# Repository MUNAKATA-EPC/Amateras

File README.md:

Munako_Amateras
2026年度：サッカーライトウェイトリーグ出場
2027年度：サッカーオープンリーグ出場予定

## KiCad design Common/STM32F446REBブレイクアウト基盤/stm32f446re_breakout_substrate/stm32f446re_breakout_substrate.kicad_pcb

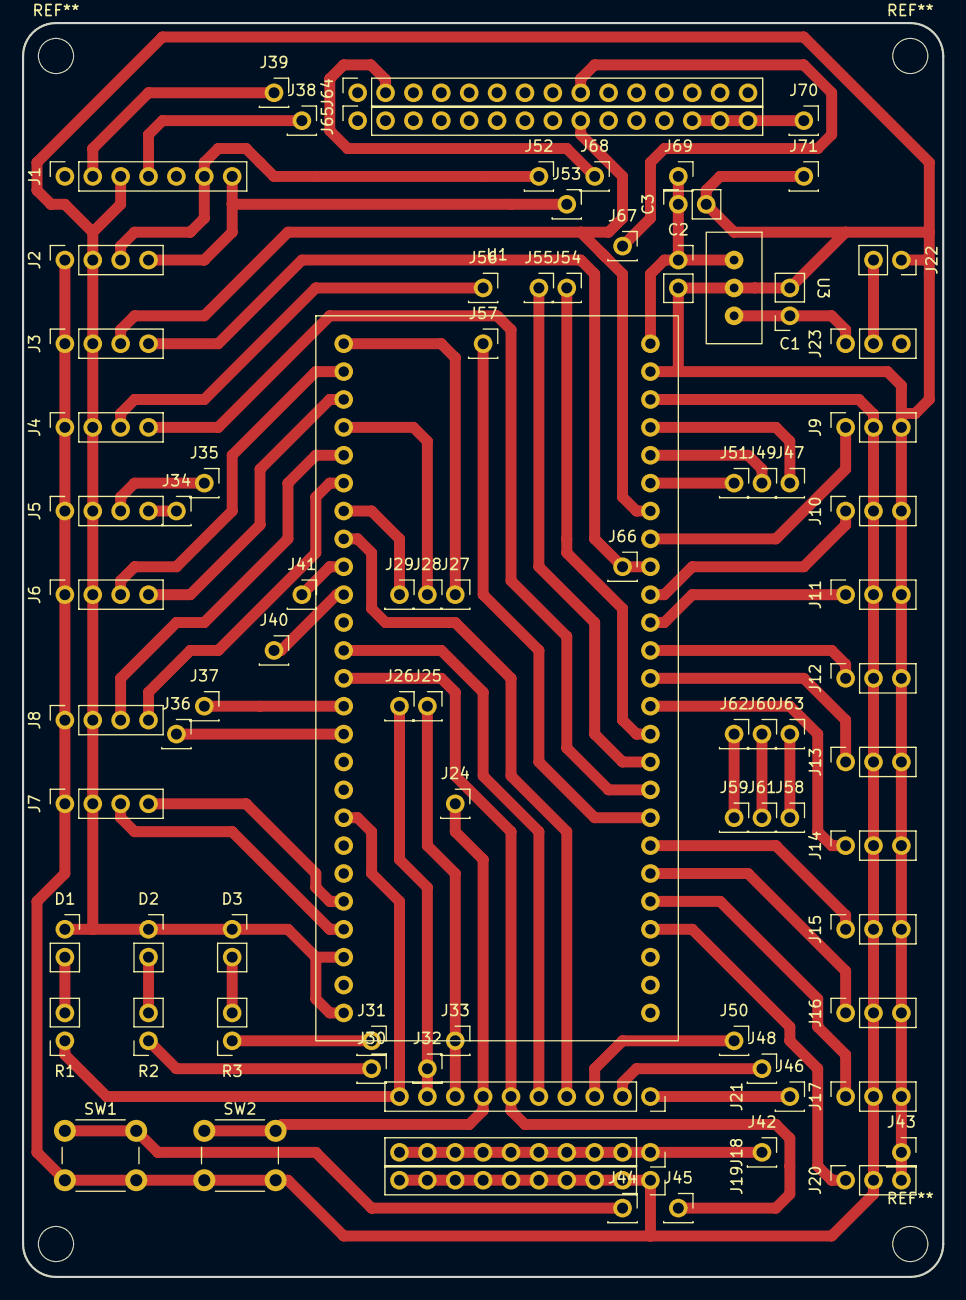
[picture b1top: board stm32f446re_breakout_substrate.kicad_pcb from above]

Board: 2 copper layers, 83.8 x 114.2 mm, 84 parts (0 on the bottom side), 67 nets.

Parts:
C1, C2: C; PinSocket_1x02_P2.54mm_Vertical
C3: C_Polarized; PinSocket_1x02_P2.54mm_Vertical
D1, D2, D3: LED; PinSocket_1x02_P2.54mm_Vertical
J1: Conn_01x07_Socket; PinSocket_1x07_P2.54mm_Vertical
J2, J3, J4, J5, J6, J7, J8: Conn_01x04_Socket; PinSocket_1x04_P2.54mm_Vertical
J9, J10, J11, J12, J13, J14, J15, J16, J17, J20, J23: Conn_01x03_Socket; PinSocket_1x03_P2.54mm_Vertical
J18, J19, J21: Conn_01x10_Socket; PinSocket_1x10_P2.54mm_Vertical
J22: Conn_01x02_Socket; PinSocket_1x02_P2.54mm_Vertical
J24: J1_B; PinSocket_1x01_P2.54mm_Vertical
J25: J2_B; PinSocket_1x01_P2.54mm_Vertical
J26: J3_B; PinSocket_1x01_P2.54mm_Vertical
J27: J1_A; PinSocket_1x01_P2.54mm_Vertical
J28: J2_A; PinSocket_1x01_P2.54mm_Vertical
J29: J3_A; PinSocket_1x01_P2.54mm_Vertical
J30: J4_B; PinSocket_1x01_P2.54mm_Vertical
J31: J5_B; PinSocket_1x01_P2.54mm_Vertical
J32: J4_A; PinSocket_1x01_P2.54mm_Vertical
J33: J5_A; PinSocket_1x01_P2.54mm_Vertical
J34: J6_B; PinSocket_1x01_P2.54mm_Vertical
J35: J7_B; PinSocket_1x01_P2.54mm_Vertical
J36: J6_A; PinSocket_1x01_P2.54mm_Vertical
J37: J7_A; PinSocket_1x01_P2.54mm_Vertical
J38: J9_B; PinSocket_1x01_P2.54mm_Vertical
J39: J8_B; PinSocket_1x01_P2.54mm_Vertical
J40: J8_A; PinSocket_1x01_P2.54mm_Vertical
J41: J9_A; PinSocket_1x01_P2.54mm_Vertical
J42: J10_B; PinSocket_1x01_P2.54mm_Vertical
J43: J10_A; PinSocket_1x01_P2.54mm_Vertical
J44: J11_B; PinSocket_1x01_P2.54mm_Vertical
J45: J11_A; PinSocket_1x01_P2.54mm_Vertical
J46: J12_B; PinSocket_1x01_P2.54mm_Vertical
J47: J12_A; PinSocket_1x01_P2.54mm_Vertical
J48: J13_B; PinSocket_1x01_P2.54mm_Vertical
J49: J13_A; PinSocket_1x01_P2.54mm_Vertical
J50: J14_B; PinSocket_1x01_P2.54mm_Vertical
J51: J14_A; PinSocket_1x01_P2.54mm_Vertical
J52: J16_B; PinSocket_1x01_P2.54mm_Vertical
J53: J15_B; PinSocket_1x01_P2.54mm_Vertical
J54: J15_A; PinSocket_1x01_P2.54mm_Vertical
J55: J16_A; PinSocket_1x01_P2.54mm_Vertical
J56: J17_B; PinSocket_1x01_P2.54mm_Vertical
J57: J17_A; PinSocket_1x01_P2.54mm_Vertical
J58, J63: J18_A; PinSocket_1x01_P2.54mm_Vertical
J59, J62: J19_A; PinSocket_1x01_P2.54mm_Vertical
J60, J61: J20_A; PinSocket_1x01_P2.54mm_Vertical
J64, J65: Conn_01x15_Socket; PinSocket_1x15_P2.54mm_Vertical
J66: J21_A; PinSocket_1x01_P2.54mm_Vertical
J67: J21_B; PinSocket_1x01_P2.54mm_Vertical
J68: J22_B; PinSocket_1x01_P2.54mm_Vertical
J69: J22_A; PinSocket_1x01_P2.54mm_Vertical
J70: J23_B; PinSocket_1x01_P2.54mm_Vertical
J71: J23_A; PinSocket_1x01_P2.54mm_Vertical
R1, R2, R3: R; PinSocket_1x02_P2.54mm_Vertical
SW1, SW2: SW_Push; SW_PUSH_6mm_H5mm
U1: STM32F446RE
U3: TO220F

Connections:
+3V3: J2.1, J3.1, J4.1, J5.1, J6.1, J7.1, J8.1, J9.2, J10.2, J11.2, J12.2, J13.2, J14.2, J15.2, J16.2, J17.2, J19.1, J19.2, J19.3, J19.4, J19.5, J19.6, J19.7, J19.8, J19.9, J19.10, J20.2, SW1.2, SW2.2, U1.3 (3V3)
+5V: C2.1, C3.1, J69.1, U1.1 (5V), U3.2 (OUT)
+9V: J22.2, J23.2
Analog/PA4: J14.1, U1.14 (Analog/PA4)
Analog/PA5: J13.1, U1.13 (Analog/PA5)
Analog/PA6: J12.1, U1.12 (Analog/PA6)
Analog/PA7: J11.1, U1.11 (Analog/PA7)
Analog/PB1: J9.1, U1.8 (Analog/PB1)
Analog/PC0: J20.1, U1.22 (Analog/PC0)
Analog/PC1: J17.1, U1.21 (Analog/PC1)
Analog/PC2: J16.1, U1.20 (Analog/PC2)
Analog/PC3: J15.1, U1.19 (Analog/PC3)
Analog/PC4: J10.1, U1.10 (Analog/PC4)
Digital/PA11: J29.1, U1.32 (Digital/PA11)
Digital/PA11/sub: J21.9, J26.1, J32.1
Digital/PA12: J21.4, U1.33 (Digital/PA12)
Digital/PB5: J21.10, R1.1, U1.43 (Digital/PB5)
Digital/PB12: J51.1, U1.6 (Digital/PB12)
Digital/PB13: J49.1, U1.5 (Dgital/PB13)
Digital/PB14: J47.1, U1.4 (Digital/PB14)
Digital/PB15: J27.1, U1.26 (Digital/PB15)
Digital/PB15/sub: J21.7, J24.1, SW2.1
Digital/PC8: J28.1, U1.29 (Digital/PC8)
Digital/PC8/sub: J21.8, J25.1, J33.1
Digital/PC10: J21.5, U1.37 (Digital/PC10)
Digital/PC11: J21.6, J45.1, U1.38 (Digital/PC11)
GND: C1.2, C2.2, C3.2, D1.1 (K), D2.1 (K), D3.1 (K), J1.3, J2.2, J3.2, J4.2, J5.2, J6.2, J7.2, J8.2, J9.3, J10.3, J11.3, J12.3, J13.3, J14.3, J15.3, J16.3, J17.3, J20.3, J22.1, J43.1, J71.1, U1.2 (GND), U1.48 (GND), U1.50 (GND), U3.3 (GND)
Main9V: C1.1, J23.1, U3.1 (IN)
unnamed: D1.2 (A), R1.2
unnamed: D2.2 (A), R2.2
unnamed: D3.2 (A), R3.2
unnamed: J1.2, J39.1
unnamed: J1.4, J38.1
unnamed: J4.3, J56.1
unnamed: J18.1, J18.2, J18.3, J18.4, J18.5, J18.6, J18.7, J18.8, J18.9, J18.10, J42.1
unnamed: J21.1, J46.1
unnamed: J21.2, J48.1
unnamed: J21.3, J50.1
unnamed: J30.1, R2.1
unnamed: J31.1, R3.1
unnamed: J5.4, J34.1
unnamed: J5.3, J35.1
unnamed: J44.1, SW1.1
unnamed: J58.1, J63.1
unnamed: J59.1, J62.1
unnamed: J60.1, J61.1
unnamed: J64.2, J68.1
unnamed: J64.9, J67.1
unnamed: J65.13, J65.14, J65.15, J70.1
RX/Serial2: J54.1, U1.15 (RX/Serial2)
RX/Serial2/sub: J1.7, J2.4, J53.1
RX/Serial3: J3.4, J66.1, U1.9 (RX/Serial3)
RX/Serial4: J4.4, U1.17 (RX/Serial4)
RX/Serial5: J36.1, U1.40 (RX/Serial5)
RX/Serial6: J6.4, U1.28 (RX/Serial6)
SCL/I2C1: J7.4, U1.46 (SCL/I2C1)
SCL/I2C3: J8.4, U1.31 (SCL/I2C3)
SDA/I2C1: J7.3, U1.47 (SDA/I2C1)
SDA/I2C3: J8.3, U1.30 (SDA/I2C3)
SWCLK: J40.1, U1.35 (SWCLK/PA14)
SWDIO: J41.1, U1.34 (SWDIO/PA13)
TX/Serial2: J55.1, U1.16 (TX/Serial2)
TX/Serial2/sub: J1.6, J2.3, J52.1
TX/Serial3: J3.3, J65.9, U1.7 (TX/Serial3)
TX/Serial4: J57.1, U1.18 (TX/Serial4)
TX/Serial5: J37.1, U1.39 (TX/Serial5)
TX/Serial6: J6.3, U1.27 (TX/Serial6)

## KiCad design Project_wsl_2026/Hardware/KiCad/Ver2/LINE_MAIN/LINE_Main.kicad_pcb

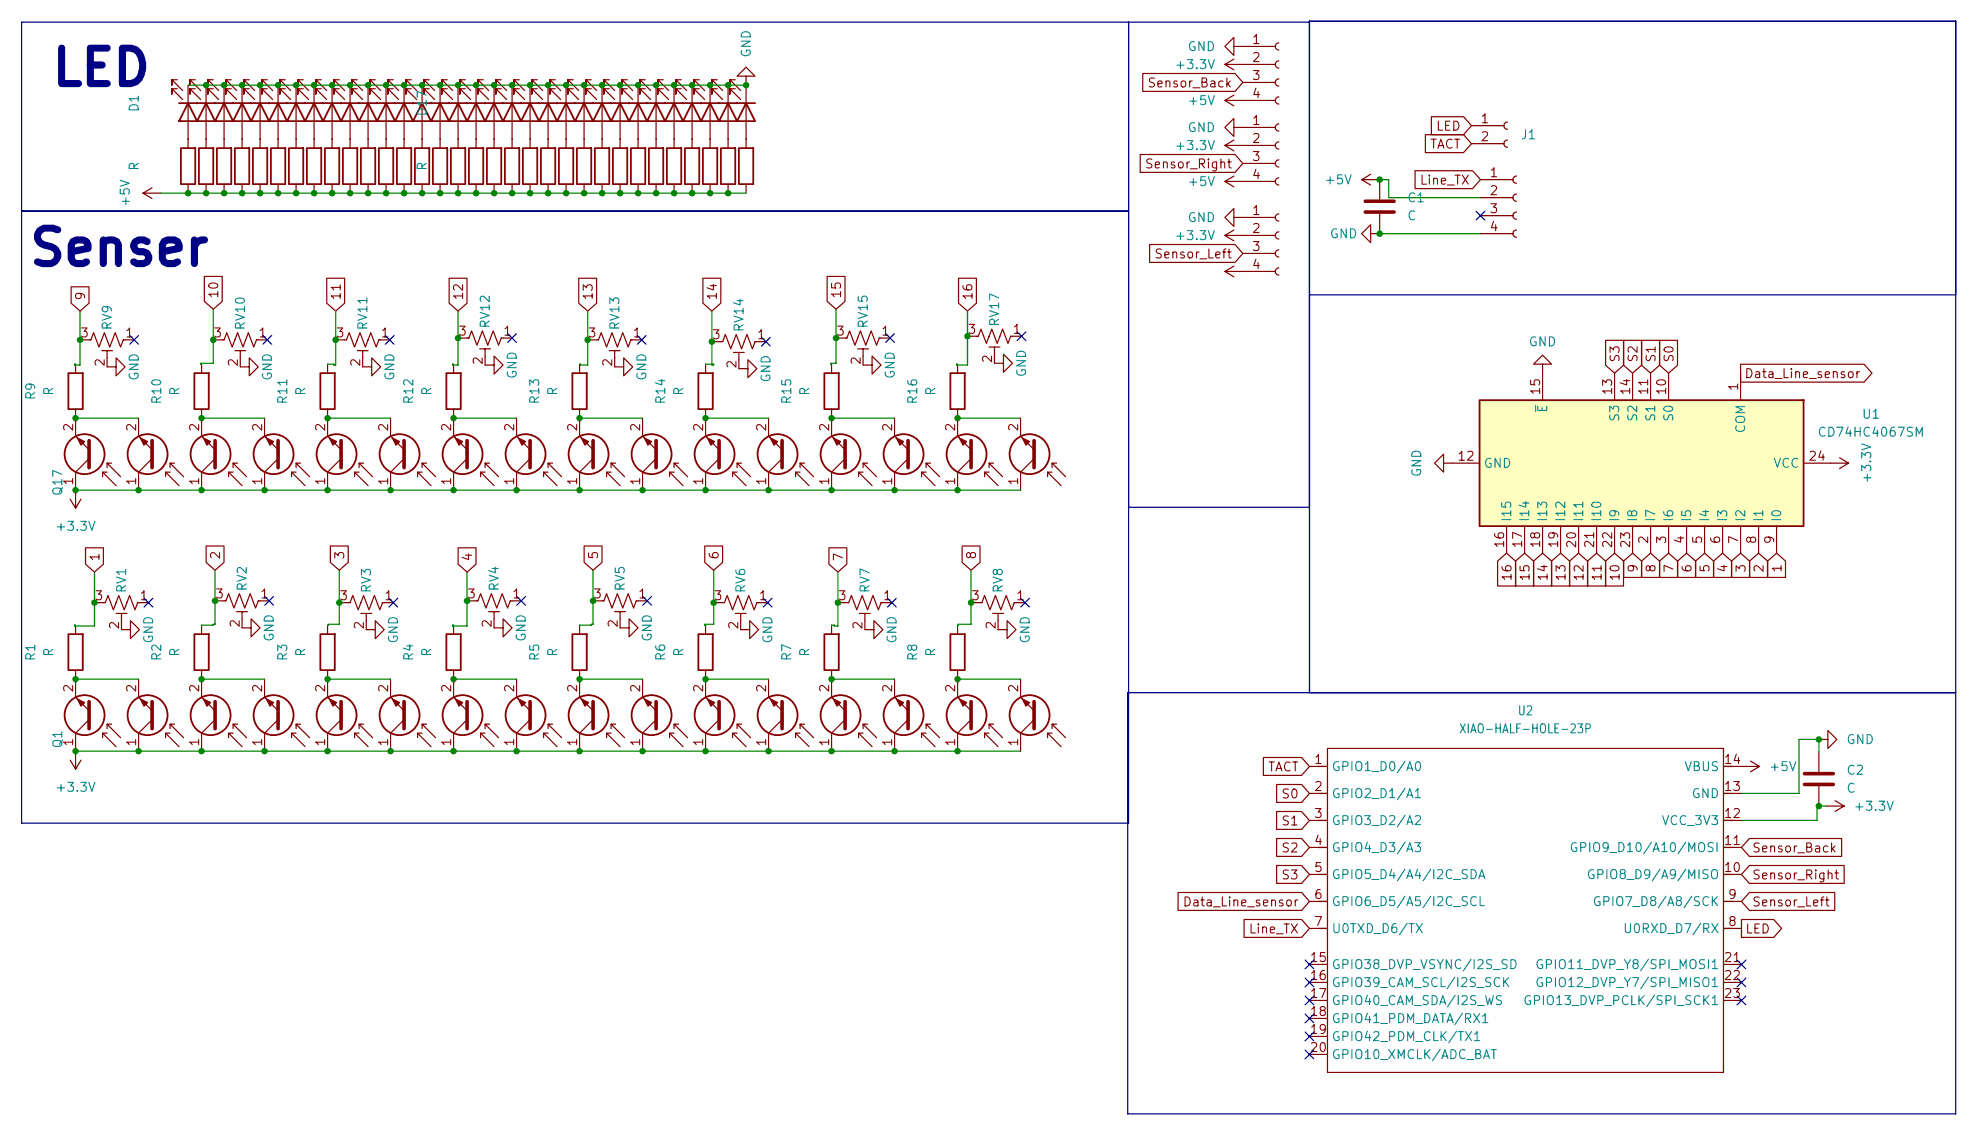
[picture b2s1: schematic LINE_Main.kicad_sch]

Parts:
C1, C2: C; PinHeader_1x02_P2.54mm_Vertical
D1, D2, D3, D4, D5, D6, D7, D8, D9, D10, D11, D12, D13, D14, D15, D16, D17, D18, D19, D20, D21, D22, D23, D24, D25, D26, D27, D28, D29, D30, D31, D32: LED; LED_D3.0mm_Clear
J1: Conn_01x02_Socket; JST_XH_B2B-XH-A_1x02_P2.50mm_Vertical
J2, J3, J4: Conn_01x04_Socket; PinHeader_1x04_P2.54mm_Vertical
J6: Conn_01x04_Socket; JST_XH_B4B-XH-A_1x04_P2.50mm_Vertical
Q1, Q2, Q3, Q4, Q5, Q6, Q7, Q8, Q9, Q10, Q11, Q12, Q13, Q14, Q15, Q16, Q17, Q18, Q19, Q20, Q21, Q22, Q23, Q24, Q25, Q26, Q27, Q28, Q29, Q30, Q31, Q32: Q_Photo_NPN; LED_D3.0mm_Clear
R1, R2, R3, R4, R5, R6, R7, R8, R9, R10, R11, R12, R13, R14, R15, R16, R17, R18, R19, R20, R21, R22, R23, R24, R25, R26, R27, R28, R29, R30, R31, R32, R33, R34, R35, R36, R37, R38, R39, R40, R41, R42, R43, R44, R45, R46, R47, R48: R; R_0805_2012Metric; LCSC C17513
RV1, RV2, RV3, RV4, RV5, RV6, RV7, RV8, RV9, RV10, RV11, RV12, RV13, RV14, RV15, RV17: R_Potentiometer_Trim_US; Potentiometer_Vishay_TS53YJ_Vertical; LCSC C719176
U1: CD74HC4067SM; SSOP-24_5.3x8.2mm_P0.65mm; LCSC C98457
U2: XIAO-HALF-HOLE-23P; Seeeduino Xiao

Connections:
1: R1.2, RV1.3, U1.9 (I0)
2: R2.2, RV2.3, U1.8 (I1)
3: R3.2, RV3.3, U1.7 (I2)
4: R4.2, RV4.3, U1.6 (I3)
5: R5.2, RV5.3, U1.5 (I4)
6: R6.2, RV6.3, U1.4 (I5)
7: R7.2, RV7.3, U1.3 (I6)
8: R8.2, RV8.3, U1.2 (I7)
9: R9.2, RV9.3, U1.23 (I8)
10: R10.2, RV10.3, U1.22 (I9)
11: R11.2, RV11.3, U1.21 (I10)
12: R12.2, RV12.3, U1.20 (I11)
13: R13.2, RV13.3, U1.19 (I12)
14: R14.2, RV14.3, U1.18 (I13)
15: R15.2, RV15.3, U1.17 (I14)
16: R16.2, RV17.3, U1.16 (I15)
+3.3V: C2.2, J2.2, J3.2, J4.2, Q1.1 (C), Q2.1 (C), Q3.1 (C), Q4.1 (C), Q5.1 (C), Q6.1 (C), Q7.1 (C), Q8.1 (C), Q9.1 (C), Q10.1 (C), Q11.1 (C), Q12.1 (C), Q13.1 (C), Q14.1 (C), Q15.1 (C), Q16.1 (C), Q17.1 (C), Q18.1 (C), Q19.1 (C), Q20.1 (C), Q21.1 (C), Q22.1 (C), Q23.1 (C), Q24.1 (C), Q25.1 (C), Q26.1 (C), Q27.1 (C), Q28.1 (C), Q29.1 (C), Q30.1 (C), Q31.1 (C), Q32.1 (C), U1.24 (VCC), U2.12 (VCC_3V3)
+5V: C1.1, J2.4, J3.4, J4.4, J6.2, R17.1, R18.1, R19.1, R20.1, R21.1, R22.1, R23.1, R24.1, R25.1, R26.1, R27.1, R28.1, R29.1, R30.1, R31.1, R32.1, R33.1, R34.1, R35.1, R36.1, R37.1, R38.1, R39.1, R40.1, R41.1, R42.1, R43.1, R44.1, R45.1, R46.1, R47.1, R48.1, U2.14 (VBUS)
Data_Line_sensor: U1.1 (COM), U2.6 (GPIO6_D5/A5/I2C_SCL)
GND: C1.2, C2.1, D1.1 (K), D2.1 (K), D3.1 (K), D4.1 (K), D5.1 (K), D6.1 (K), D7.1 (K), D8.1 (K), D9.1 (K), D10.1 (K), D11.1 (K), D12.1 (K), D13.1 (K), D14.1 (K), D15.1 (K), D16.1 (K), D17.1 (K), D18.1 (K), D19.1 (K), D20.1 (K), D21.1 (K), D22.1 (K), D23.1 (K), D24.1 (K), D25.1 (K), D26.1 (K), D27.1 (K), D28.1 (K), D29.1 (K), D30.1 (K), D31.1 (K), D32.1 (K), J2.1, J3.1, J4.1, J6.4, RV1.2, RV2.2, RV3.2, RV4.2, RV5.2, RV6.2, RV7.2, RV8.2, RV9.2, RV10.2, RV11.2, RV12.2, RV13.2, RV14.2, RV15.2, RV17.2, U1.12 (GND), U1.15 (~E), U2.13 (GND)
LED: J1.1, U2.8 (U0RXD_D7/RX)
Line_TX: J6.1, U2.7 (U0TXD_D6/TX)
unnamed: D1.2 (A), R17.2
unnamed: D2.2 (A), R18.2
unnamed: D3.2 (A), R19.2
unnamed: D4.2 (A), R20.2
unnamed: D5.2 (A), R21.2
unnamed: D6.2 (A), R22.2
unnamed: D7.2 (A), R23.2
unnamed: D8.2 (A), R24.2
unnamed: D9.2 (A), R25.2
unnamed: D10.2 (A), R26.2
unnamed: D11.2 (A), R27.2
unnamed: D12.2 (A), R28.2
unnamed: D13.2 (A), R29.2
unnamed: D14.2 (A), R30.2
unnamed: D15.2 (A), R31.2
unnamed: D16.2 (A), R32.2
unnamed: D17.2 (A), R33.2
unnamed: D18.2 (A), R34.2
unnamed: D19.2 (A), R35.2
unnamed: D20.2 (A), R36.2
unnamed: D21.2 (A), R37.2
unnamed: D22.2 (A), R38.2
unnamed: D23.2 (A), R39.2
unnamed: D24.2 (A), R40.2
unnamed: D25.2 (A), R41.2
unnamed: D26.2 (A), R42.2
unnamed: D27.2 (A), R43.2
unnamed: D28.2 (A), R44.2
unnamed: D29.2 (A), R45.2
unnamed: D30.2 (A), R46.2
unnamed: D31.2 (A), R47.2
unnamed: D32.2 (A), R48.2
unnamed: Q1.2 (E), Q2.2 (E), R1.1
unnamed: Q3.2 (E), Q4.2 (E), R2.1
unnamed: Q5.2 (E), Q6.2 (E), R3.1
unnamed: Q7.2 (E), Q8.2 (E), R4.1
unnamed: Q9.2 (E), Q10.2 (E), R5.1
unnamed: Q11.2 (E), Q12.2 (E), R6.1
unnamed: Q13.2 (E), Q14.2 (E), R7.1
unnamed: Q15.2 (E), Q16.2 (E), R8.1
unnamed: Q17.2 (E), Q18.2 (E), R9.1
unnamed: Q19.2 (E), Q20.2 (E), R10.1
unnamed: Q21.2 (E), Q22.2 (E), R11.1
unnamed: Q23.2 (E), Q24.2 (E), R12.1
unnamed: Q25.2 (E), Q26.2 (E), R13.1
unnamed: Q27.2 (E), Q28.2 (E), R14.1
unnamed: Q29.2 (E), Q30.2 (E), R15.1
unnamed: Q31.2 (E), Q32.2 (E), R16.1
S0: U1.10 (S0), U2.2 (GPIO2_D1/A1)
S1: U1.11 (S1), U2.3 (GPIO3_D2/A2)
S2: U1.14 (S2), U2.4 (GPIO4_D3/A3)
S3: U1.13 (S3), U2.5 (GPIO5_D4/A4/I2C_SDA)
Sensor_Back: J2.3, U2.11 (GPIO9_D10/A10/MOSI)
Sensor_Left: J4.3, U2.9 (GPIO7_D8/A8/SCK)
Sensor_Right: J3.3, U2.10 (GPIO8_D9/A9/MISO)
TACT: J1.2, U2.1 (GPIO1_D0/A0)

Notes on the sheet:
LED
Senser

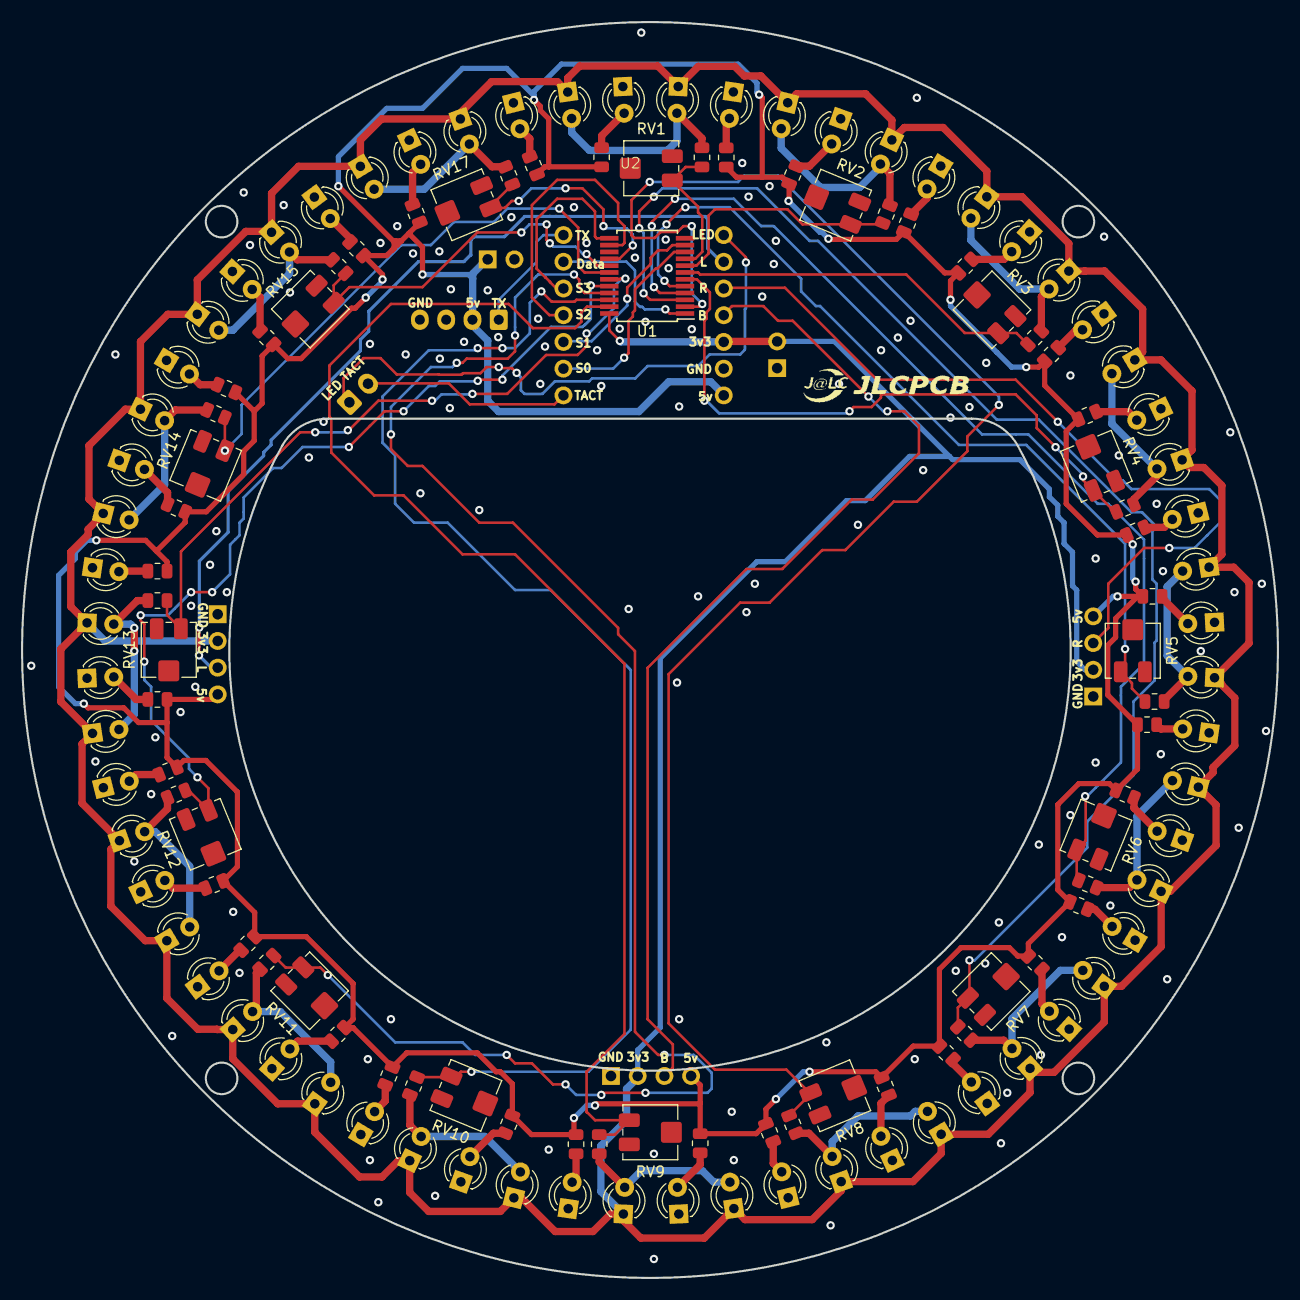
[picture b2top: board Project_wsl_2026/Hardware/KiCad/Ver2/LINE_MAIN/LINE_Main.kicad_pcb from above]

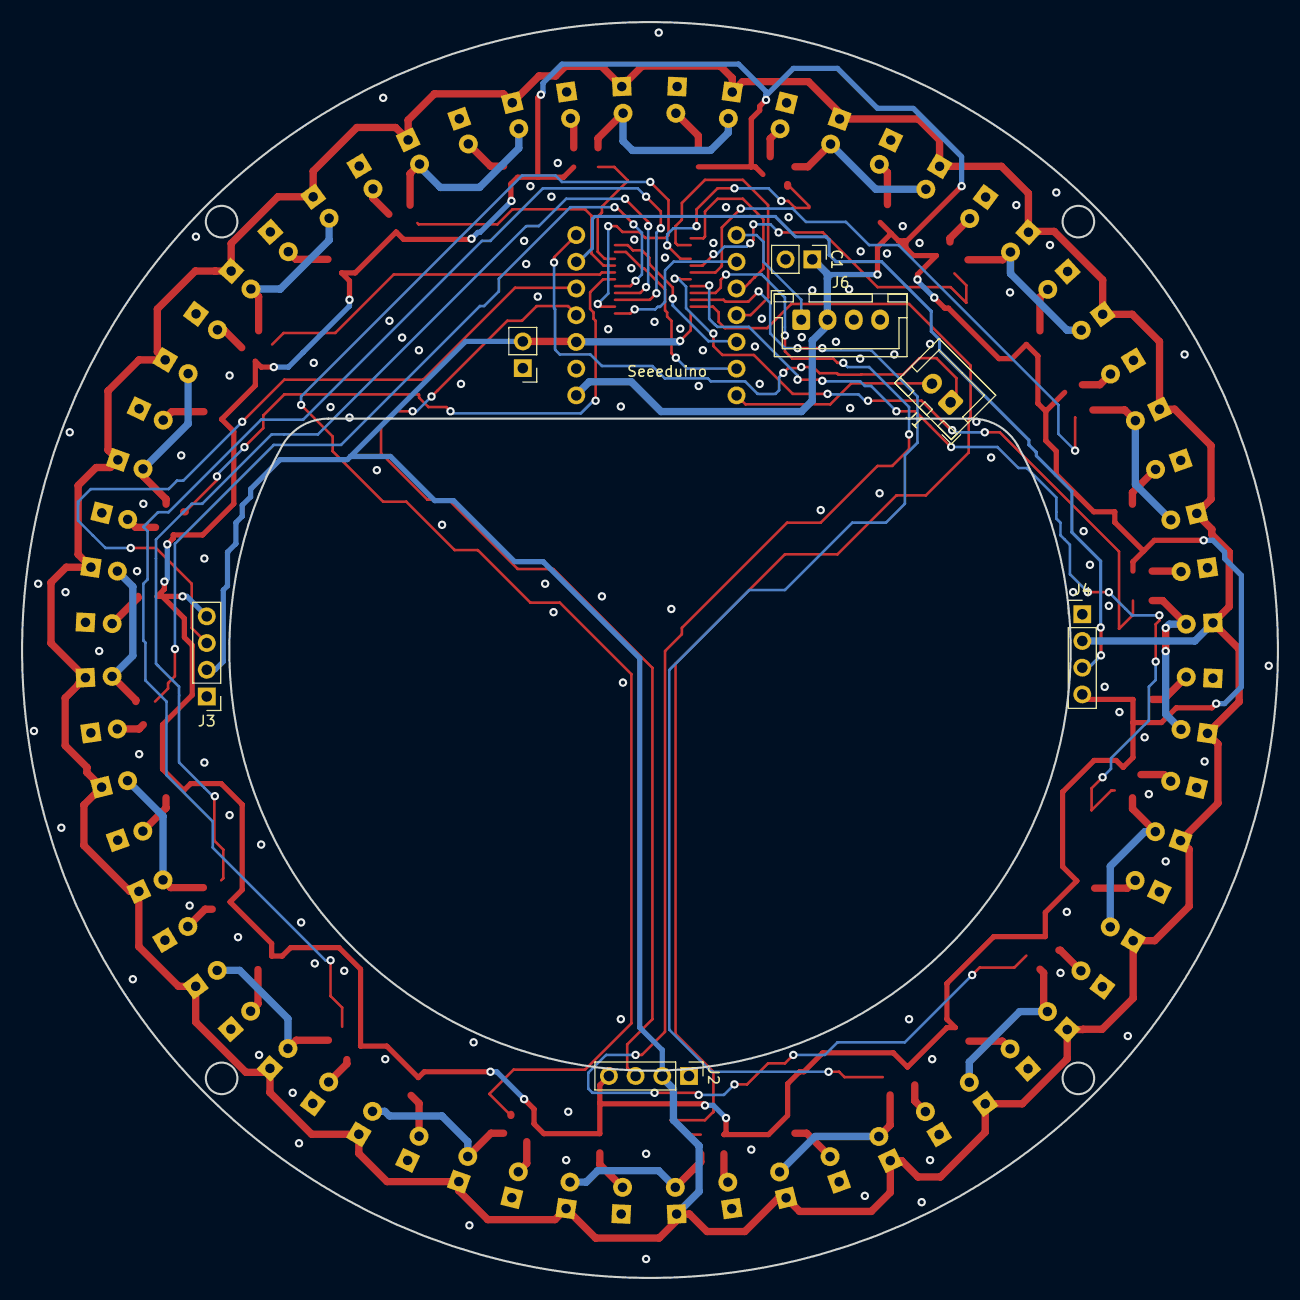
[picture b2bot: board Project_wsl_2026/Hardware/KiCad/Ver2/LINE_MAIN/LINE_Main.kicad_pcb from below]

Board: 2 copper layers, 119.4 x 119.4 mm, 137 parts (7 on the bottom side), 78 nets.

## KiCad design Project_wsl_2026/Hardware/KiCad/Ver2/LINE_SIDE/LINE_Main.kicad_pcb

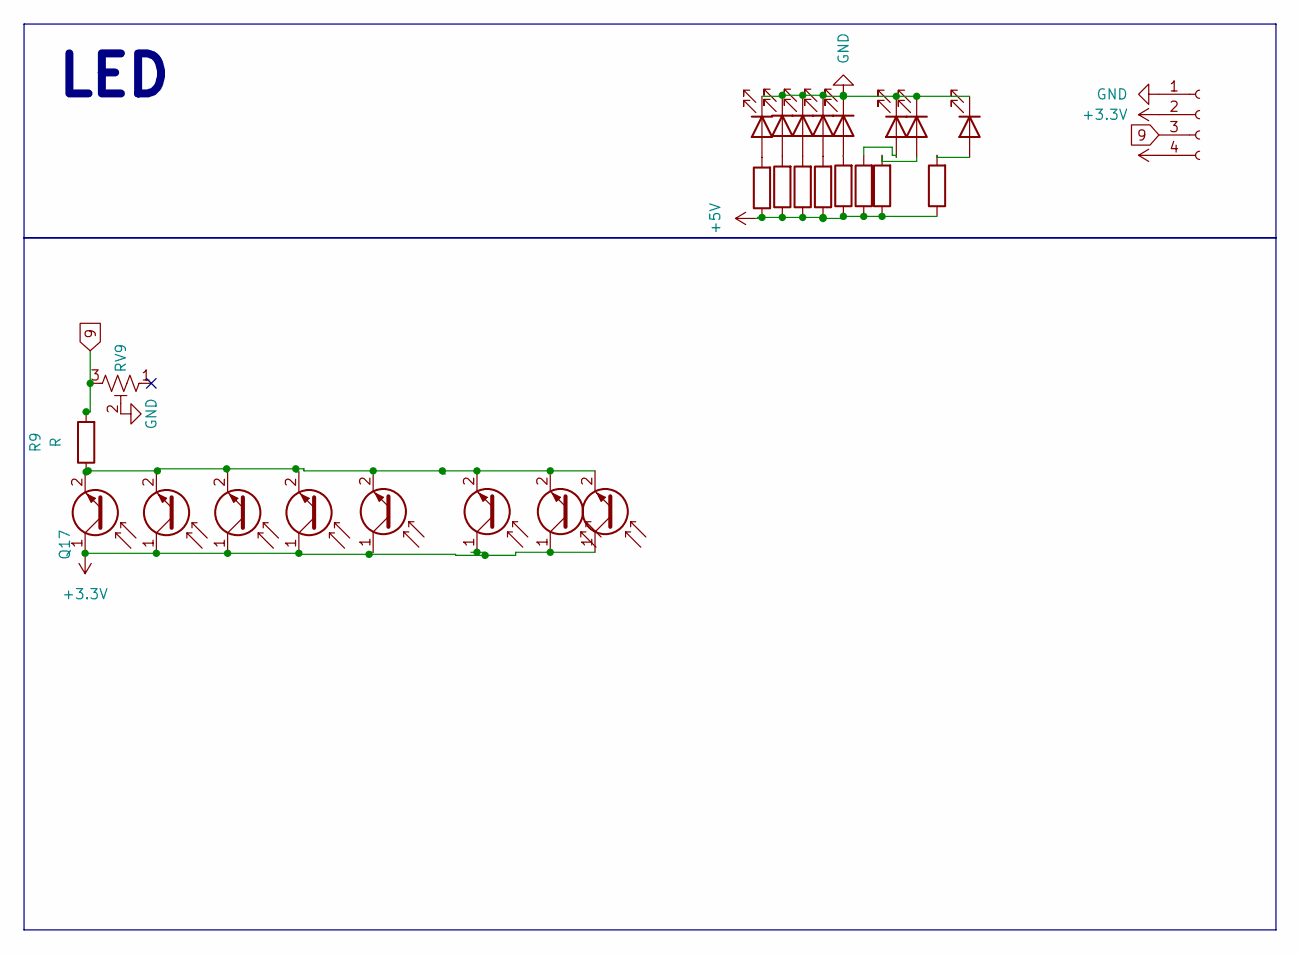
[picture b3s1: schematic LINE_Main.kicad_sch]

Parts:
D1, D2, D3, D4, D29, D30, D31, D32: LED; LED_D3.0mm_Clear
J4: Conn_01x04_Socket; PinHeader_1x04_P2.54mm_Horizontal
Q1, Q2, Q3, Q17, Q18, Q19, Q20, Q21: Q_Photo_NPN; LED_D3.0mm_Clear
R1, R2, R3, R9, R44, R45, R46, R47, R48: R; R_0805_2012Metric; LCSC C17513
RV9: R_Potentiometer_Trim_US; Potentiometer_Vishay_TS53YJ_Vertical; LCSC C719176

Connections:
9: J4.3, R9.2, RV9.3
+3.3V: J4.2, Q1.1 (C), Q2.1 (C), Q3.1 (C), Q17.1 (C), Q18.1 (C), Q19.1 (C), Q20.1 (C), Q21.1 (C)
+5V: J4.4, R1.1, R2.1, R3.1, R44.1, R45.1, R46.1, R47.1, R48.1
GND: D1.1 (K), D2.1 (K), D3.1 (K), D4.1 (K), D29.1 (K), D30.1 (K), D31.1 (K), D32.1 (K), J4.1, RV9.2
unnamed: D1.2 (A), R44.2
unnamed: D2.2 (A), R1.2
unnamed: D3.2 (A), R2.2
unnamed: D4.2 (A), R3.2
unnamed: D29.2 (A), R45.2
unnamed: D30.2 (A), R46.2
unnamed: D31.2 (A), R47.2
unnamed: D32.2 (A), R48.2
unnamed: Q1.2 (E), Q2.2 (E), Q3.2 (E), Q17.2 (E), Q18.2 (E), Q19.2 (E), Q20.2 (E), Q21.2 (E), R9.1

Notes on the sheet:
LED

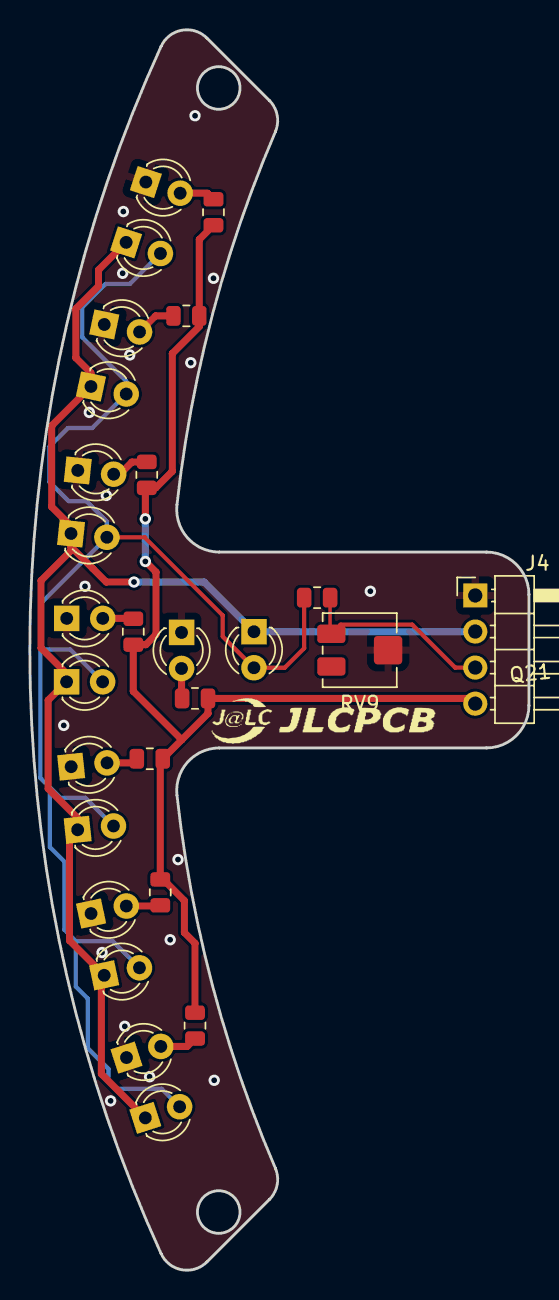
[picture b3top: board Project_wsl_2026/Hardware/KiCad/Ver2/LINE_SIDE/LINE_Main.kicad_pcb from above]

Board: 2 copper layers, 35.2 x 87.4 mm, 27 parts (0 on the bottom side), 13 nets.

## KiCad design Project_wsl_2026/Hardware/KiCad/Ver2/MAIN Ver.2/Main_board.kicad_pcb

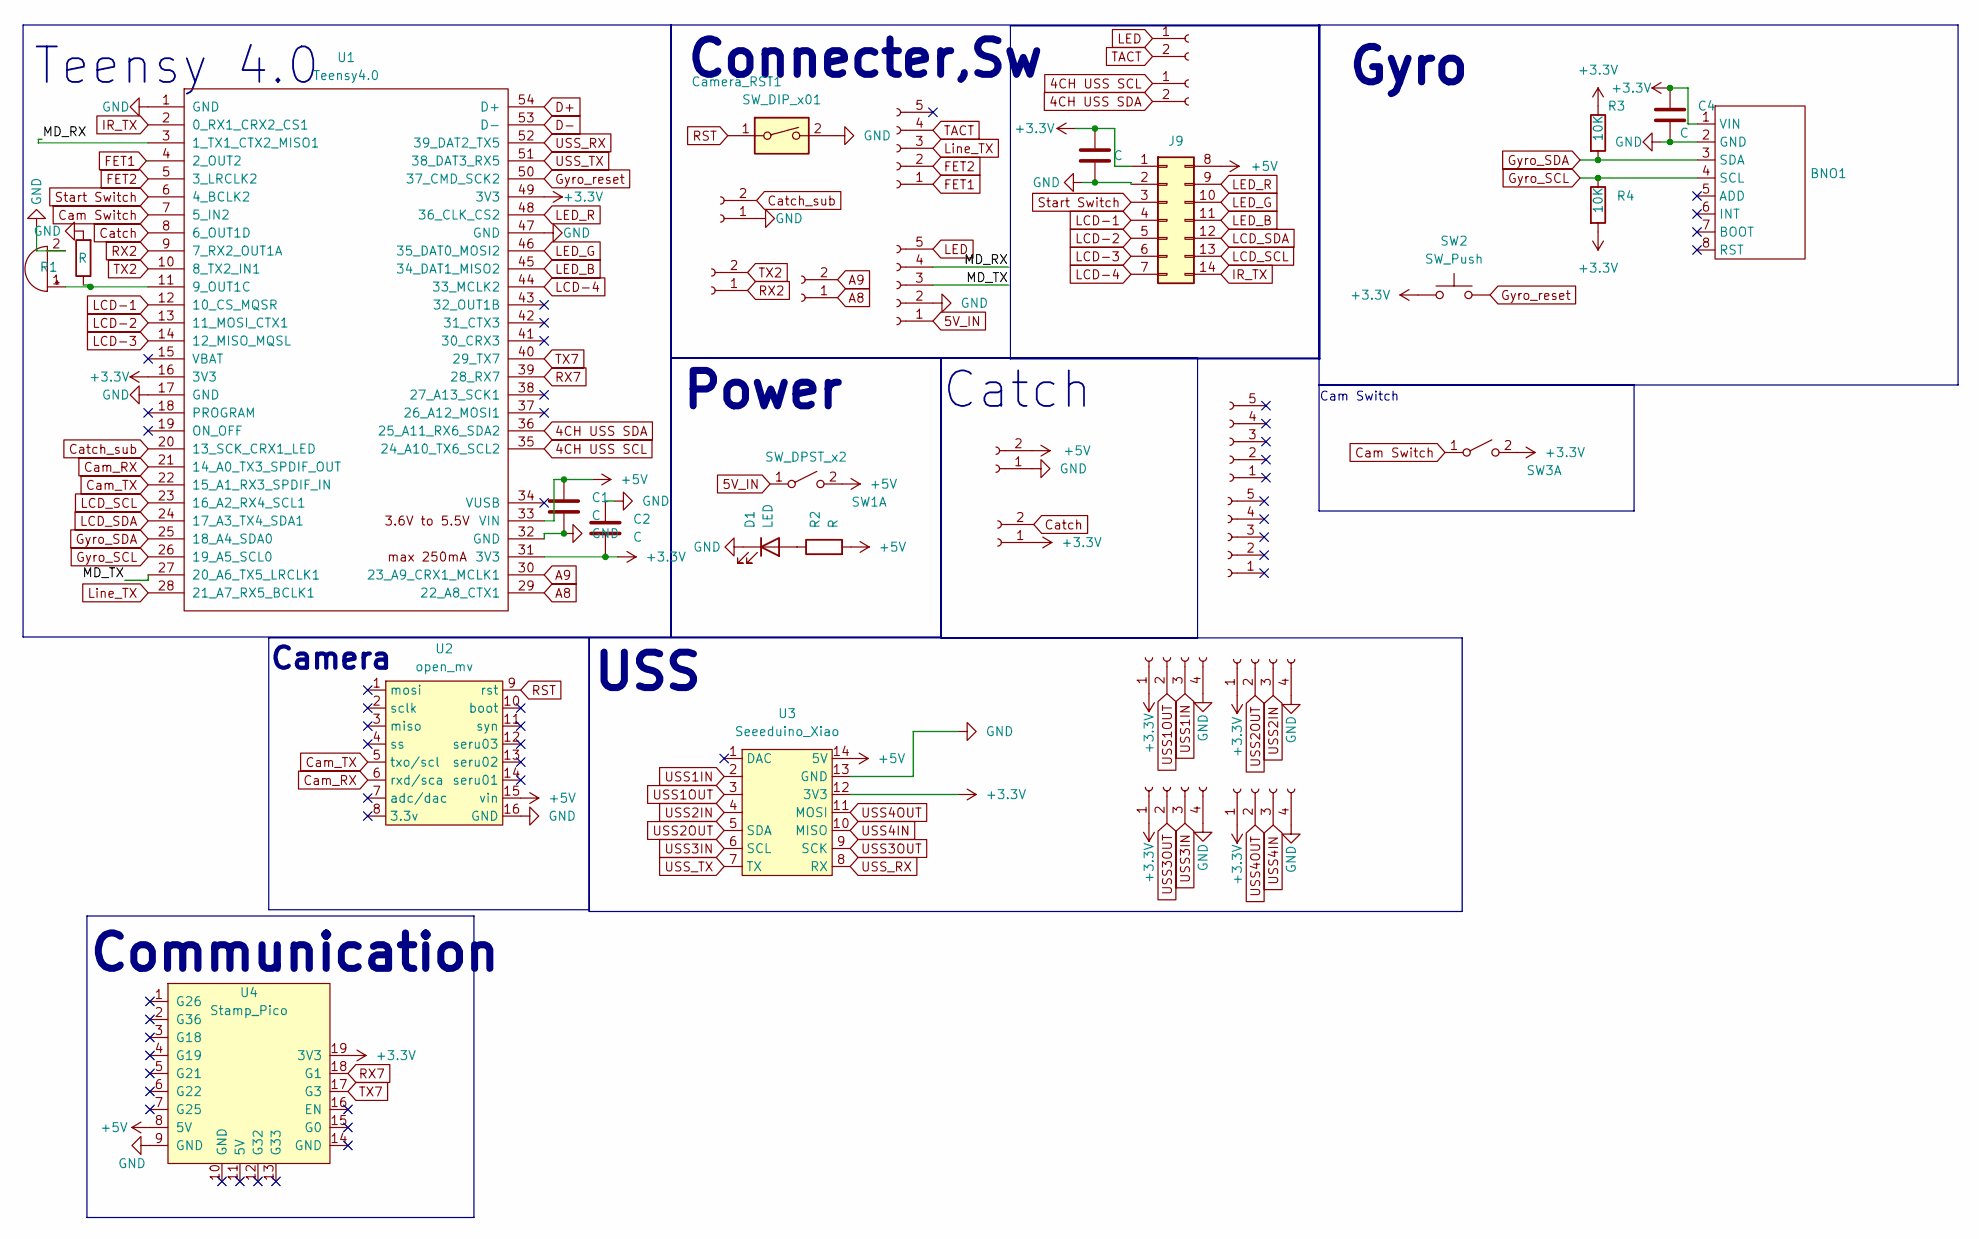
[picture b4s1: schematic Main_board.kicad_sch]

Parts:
BNO1: BNO055
BZ1: Buzzer; Buzzer_12x9.5RM7.6
C1, C2, C4: C; C_Disc_D3.8mm_W2.6mm_P2.50mm
C3: C; C_Disc_D5.0mm_W2.5mm_P2.50mm
Camera_RST1: SW_DIP_x01; SW_PUSH_6mm_H5mm
D1: LED; LED_D3.0mm_Clear
J1, J2, J3, J6, J7, J8, J12: Conn_01x02_Socket; JST_XH_B2B-XH-A_1x02_P2.50mm_Vertical
J4, J5, J13, J14: Conn_01x05_Socket; PinHeader_1x05_P2.54mm_Vertical
J9: Conn_02x07_Top_Bottom; IDC-Header_2x07_P2.54mm_Vertical
J10, J11, J15, J16: Conn_01x04_Socket; JST_XH_B4B-XH-A_1x04_P2.50mm_Vertical
R1: R; R_Axial_DIN0204_L3.6mm_D1.6mm_P5.08mm_Horizontal
R2: R; R_Axial_DIN0204_L3.6mm_D1.6mm_P5.08mm_Vertical
R3, R4: 10K; R_Axial_DIN0204_L3.6mm_D1.6mm_P5.08mm_Vertical
SW1, SW3: SW_DPST_x2; PinSocket_1x03_P2.54mm_Vertical
SW2: SW_Push; SW_PUSH_6mm_H5mm
U1: Teensy4.0; Tennsy4.0 Breakout
U2: open_mv; 名称未設定_1
U3: Seeeduino_Xiao; Seeeduino Xiao
U4: Stamp_Pico; M5 Stamp Pico

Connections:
4CH USS SCL: J8.1, U1.35 (24_A10_TX6_SCL2)
4CH USS SDA: J8.2, U1.36 (25_A11_RX6_SDA2)
5V_IN: J5.1, SW1.1 (A)
+3.3V: BNO1.1 (VIN), C2.2, C3.1, C4.1, J7.1, J9.1, J10.1, J11.1, J15.1, J16.1, R3.1, R4.2, SW2.1, SW3.2 (B), U1.16 (3V3), U1.31 (3V3), U1.49 (3V3), U3.12 (3V3), U4.19 (3V3)
+5V: C1.1, J6.2, J9.8, R2.2, SW1.2 (B), U1.33 (VIN), U2.15 (vin), U3.14 (5V), U4.8 (5V)
/MD_RX: J5.4, U1.3 (1_TX1_CTX2_MISO1)
/MD_TX: J5.3, U1.27 (20_A6_TX5_LRCLK1)
A8: J3.1, U1.29 (22_A8_CTX1)
A9: J3.2, U1.30 (23_A9_CRX1_MCLK1)
Cam Switch: SW3.1 (A), U1.7 (5_IN2)
Cam_RX: U1.21 (14_A0_TX3_SPDIF_OUT), U2.6 (rxd/sca)
Cam_TX: U1.22 (15_A1_RX3_SPDIF_IN), U2.5 (txo/scl)
Catch: J7.2, U1.8 (6_OUT1D)
Catch_sub: J2.2, U1.20 (13_SCK_CRX1_LED)
D+: U1.54 (D+)
D-: U1.53 (D-)
FET1: J4.1, U1.4 (2_OUT2)
FET2: J4.2, U1.5 (3_LRCLK2)
GND: BNO1.2 (GND), BZ1.2 (+), C1.2, C2.1, C3.2, C4.2, Camera_RST1.2, D1.1 (K), J2.1, J5.2, J6.1, J9.2, J10.4, J11.4, J15.4, J16.4, R1.2, U1.1 (GND), U1.17 (GND), U1.32 (GND), U1.47 (GND), U2.16 (GND), U3.13 (GND), U4.9 (GND)
Gyro_SCL: BNO1.4 (SCL), R4.1, U1.26 (19_A5_SCL0)
Gyro_SDA: BNO1.3 (SDA), R3.2, U1.25 (18_A4_SDA0)
Gyro_reset: SW2.2, U1.50 (37_CMD_SCK2)
IR_TX: J9.14, U1.2 (0_RX1_CRX2_CS1)
LCD-1: J9.4, U1.12 (10_CS_MQSR)
LCD-2: J9.5, U1.13 (11_MOSI_CTX1)
LCD-3: J9.6, U1.14 (12_MISO_MQSL)
LCD-4: J9.7, U1.44 (33_MCLK2)
LCD_SCL: J9.13, U1.23 (16_A2_RX4_SCL1)
LCD_SDA: J9.12, U1.24 (17_A3_TX4_SDA1)
LED: J5.5, J12.1
LED_B: J9.11, U1.45 (34_DAT1_MISO2)
LED_G: J9.10, U1.46 (35_DAT0_MOSI2)
LED_R: J9.9, U1.48 (36_CLK_CS2)
Line_TX: J4.3, U1.28 (21_A7_RX5_BCLK1)
unnamed: BZ1.1 (-), R1.1, U1.11 (9_OUT1C)
unnamed: D1.2 (A), R2.1
RST: Camera_RST1.1, U2.9 (rst)
RX2: J1.1, U1.9 (7_RX2_OUT1A)
RX7: U1.39 (28_RX7), U4.18 (G1)
Start Switch: J9.3, U1.6 (4_BCLK2)
TACT: J4.4, J12.2
TX2: J1.2, U1.10 (8_TX2_IN1)
TX7: U1.40 (29_TX7), U4.17 (G3)
USS1IN: J10.3, U3.2
USS1OUT: J10.2, U3.3
USS2IN: J15.3, U3.4
USS2OUT: J15.2, U3.5 (SDA)
USS3IN: J11.3, U3.6 (SCL)
USS3OUT: J11.2, U3.9 (SCK)
USS4IN: J16.3, U3.10 (MISO)
USS4OUT: J16.2, U3.11 (MOSI)
USS_RX: U1.52 (39_DAT2_TX5), U3.8 (RX)
USS_TX: U1.51 (38_DAT3_RX5), U3.7 (TX)

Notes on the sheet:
Cam Switch
Power
Camera
Communication
Teensy 4.0
Catch
Connecter,Sw
USS
Gyro
